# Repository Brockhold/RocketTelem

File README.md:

# CSS427-Project
# Team Rocket

### Members
**Robert Bachta**
**Ben Rockhold**

### Hardware / Sensors
- Adafruit Feather M0 Bluefruit
- Adafruit Feather M0 Adalogger
- (2) Sparkfun RFM69HCW 915MHz Wireless Transceiver
- Ultimate GPS Breakout v3
- Adafruit 10 DOF (LSM303DLHC Accel/Mag, L3GD20H Gyroscope, BMP180 Temp/Baro)

### Software
- Adafruit_GPS.h
- Adafruit_Sensor.h
- Adafruit_LSM303_U.h
- Adafruit_BMP085_U.h
- Adafruit_L3GD20_U.h
- Adafruit_10DOF.h
- RH_RF69.h

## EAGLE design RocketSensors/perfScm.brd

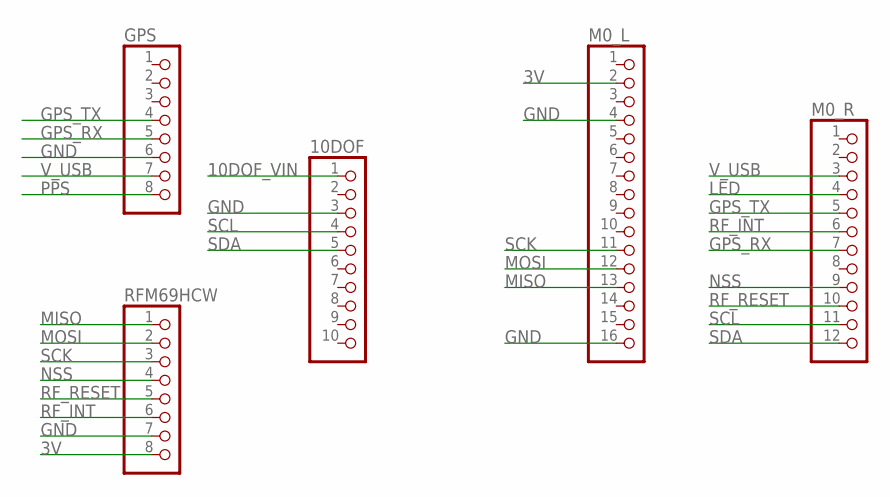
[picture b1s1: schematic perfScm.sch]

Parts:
10DOF: PINHD-1X10; 1X10
GPS: PINHD-1X8; 1X08
M0_L: PINHD-1X16; 1X16
M0_R: PINHD-1X12; 1X12
RFM69HCW: PINHD-1X8; 1X08

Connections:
3V: M0_L.2, RFM69HCW.8
10DOF_VIN: 10DOF.1
GND: 10DOF.3, GPS.6, M0_L.4, M0_L.16, RFM69HCW.7
GPS_RX: GPS.5, M0_R.7
GPS_TX: GPS.4, M0_R.5
LED: M0_R.4
MISO: M0_L.13, RFM69HCW.1
MOSI: M0_L.12, RFM69HCW.2
NSS: M0_R.9, RFM69HCW.4
PPS: GPS.8
RF_INT: M0_R.6, RFM69HCW.6
RF_RESET: M0_R.10, RFM69HCW.5
SCK: M0_L.11, RFM69HCW.3
SCL: 10DOF.4, M0_R.11
SDA: 10DOF.5, M0_R.12
V_USB: GPS.7, M0_R.3

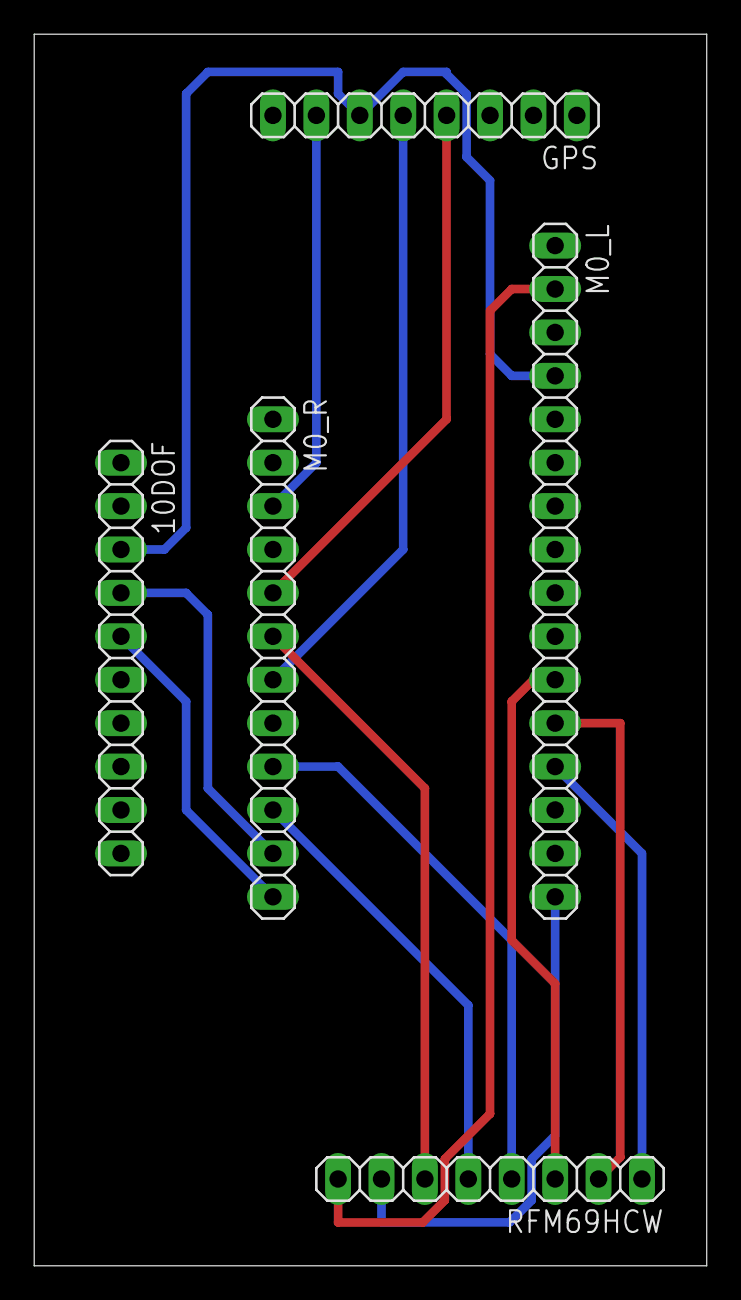
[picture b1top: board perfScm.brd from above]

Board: 2 copper layers, 39.4 x 72.1 mm, 5 parts (0 on the bottom side), 13 nets.

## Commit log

2018-10-02 Initial commit for GPS_TX
    First prototype for sensor reading and radio transmission. Successfully implements UART mapping for connecting the GPS to a dedicated hardware serial port, and communicates with the RFM69HCW radio vi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
2018-10-02 Initial commit of GPS_RX
    Simple sketch to read all messages from the RFM69HCW radio over SPI and dump them to serial for the host to look at. Performs some janky message parsing, which does not appear to work.
2018-10-03 Minor printout formatting changes
2018-10-04 rewrote packet encoding and decoding, uses uint8 but still assigns without proper breaking up
2018-10-07 updated TX/RX process
2018-10-07 updated messaging & code structure
2018-10-09 Updated fixed decimal conversion
    Minor corrections to printout and packet decode. GPS position is now printed accurately, and in standard format.
2018-10-09 General cleanup
2018-10-10 Rearranged TX program
    Moved all #define into a seperate config file, updated comments, corrected location of some config methods and their order.
    Also added SD card initialization, not currently used anywhere.
2018-10-18 Swapped out shitty math for casting a struct to the data type of the packet
2018-10-18 Added config and decode to RX, expaned both to cover floats.
2018-11-08 Initial re-arranging TX code for 10-dof sensor
2018-11-16 expanded commets for RX, added empty method for initSensors() in TX
2018-11-16 added simple init routine to TX
2018-11-16 updated TX and RX struct to reflect 10dof sensors
2018-11-16 removed RX prints for sensors that do not exist
2018-11-16 Added prints for added structure values.
2018-11-16 TX/RX structure update to reduce redundant heading
2018-11-16 jammed sensors into TX message, added same to debug printout
2018-11-17 Beginning stages of polling system. Additional work required. WIP
2018-11-17 abstracted various tasks for readability. Added Message ID to payload.
2018-11-21 Updated polling mechanism. Clean up more code.
2018-11-21 added battery voltage byte to encode/decode headers
2018-11-25 rearranged some logic in RX, slight change to UI
    Removed the feature for user entering '1' because it's redundant with '0'. Also, sending an empty string is the same as sending 0, because of what parseInt() returns.
2018-11-25 Added #define for minimum valid polling time
    Not currently matched on TX side, where it is hard-coded.
2018-11-25 nobody saw that
2018-11-25 Partly reverted some logic mistakes, updated usage message
2018-11-25 comment re-arrange
    also enabled debug for TX-side
2018-11-26 changed logic of onDemand polling
    sending either 0 or '' will trigger an update, but the system still loops to make sure GPS is up to date.
2018-11-26 Added battery voltage measurement and reporting
    +1 sensor, yay
2018-11-26 Minor comment changes for RX printout readability
    logic unchanged, but printout much more readable (and has dumb HTML-like headers too...)
2018-11-26 yet more trivial comment changes
2018-11-26 why did I write 'us' instead of 'ms' ???
2018-11-30 added type cast and scaling to the pitch/roll/heading values prior to transmission
2018-11-30 fixed a single-character bug preventing 10Hz updates...
2018-12-02 swap pitch and roll to unsigned ints
2018-12-02 Revert "swap pitch and roll to unsigned ints"
    This reverts commit 8f3b353b672997278dfbee4f86e86ccf2ba49c5d.
2018-12-02 use signed ints for pitch and roll so they can go negative
    second commit...
2018-12-07 Started to shove SD card functions into the TX side of things
2018-12-09 Added SD card packet TX & RX. functionality doesnt exist, just the commands are currently sending
2018-12-10 Added SD card functionality. Ability to enable, disable, erase, create new
2018-12-10 Added bluetooth mirroring for status messages.
    Note that polling rates above 1/second are pretty much useless due to slow speed of BTLE.
2018-12-11 reduced btle prints slightly
2018-12-11 added fake GPS (000.0000) when indoors
2019-01-25 Added circuit schematic because well why not
